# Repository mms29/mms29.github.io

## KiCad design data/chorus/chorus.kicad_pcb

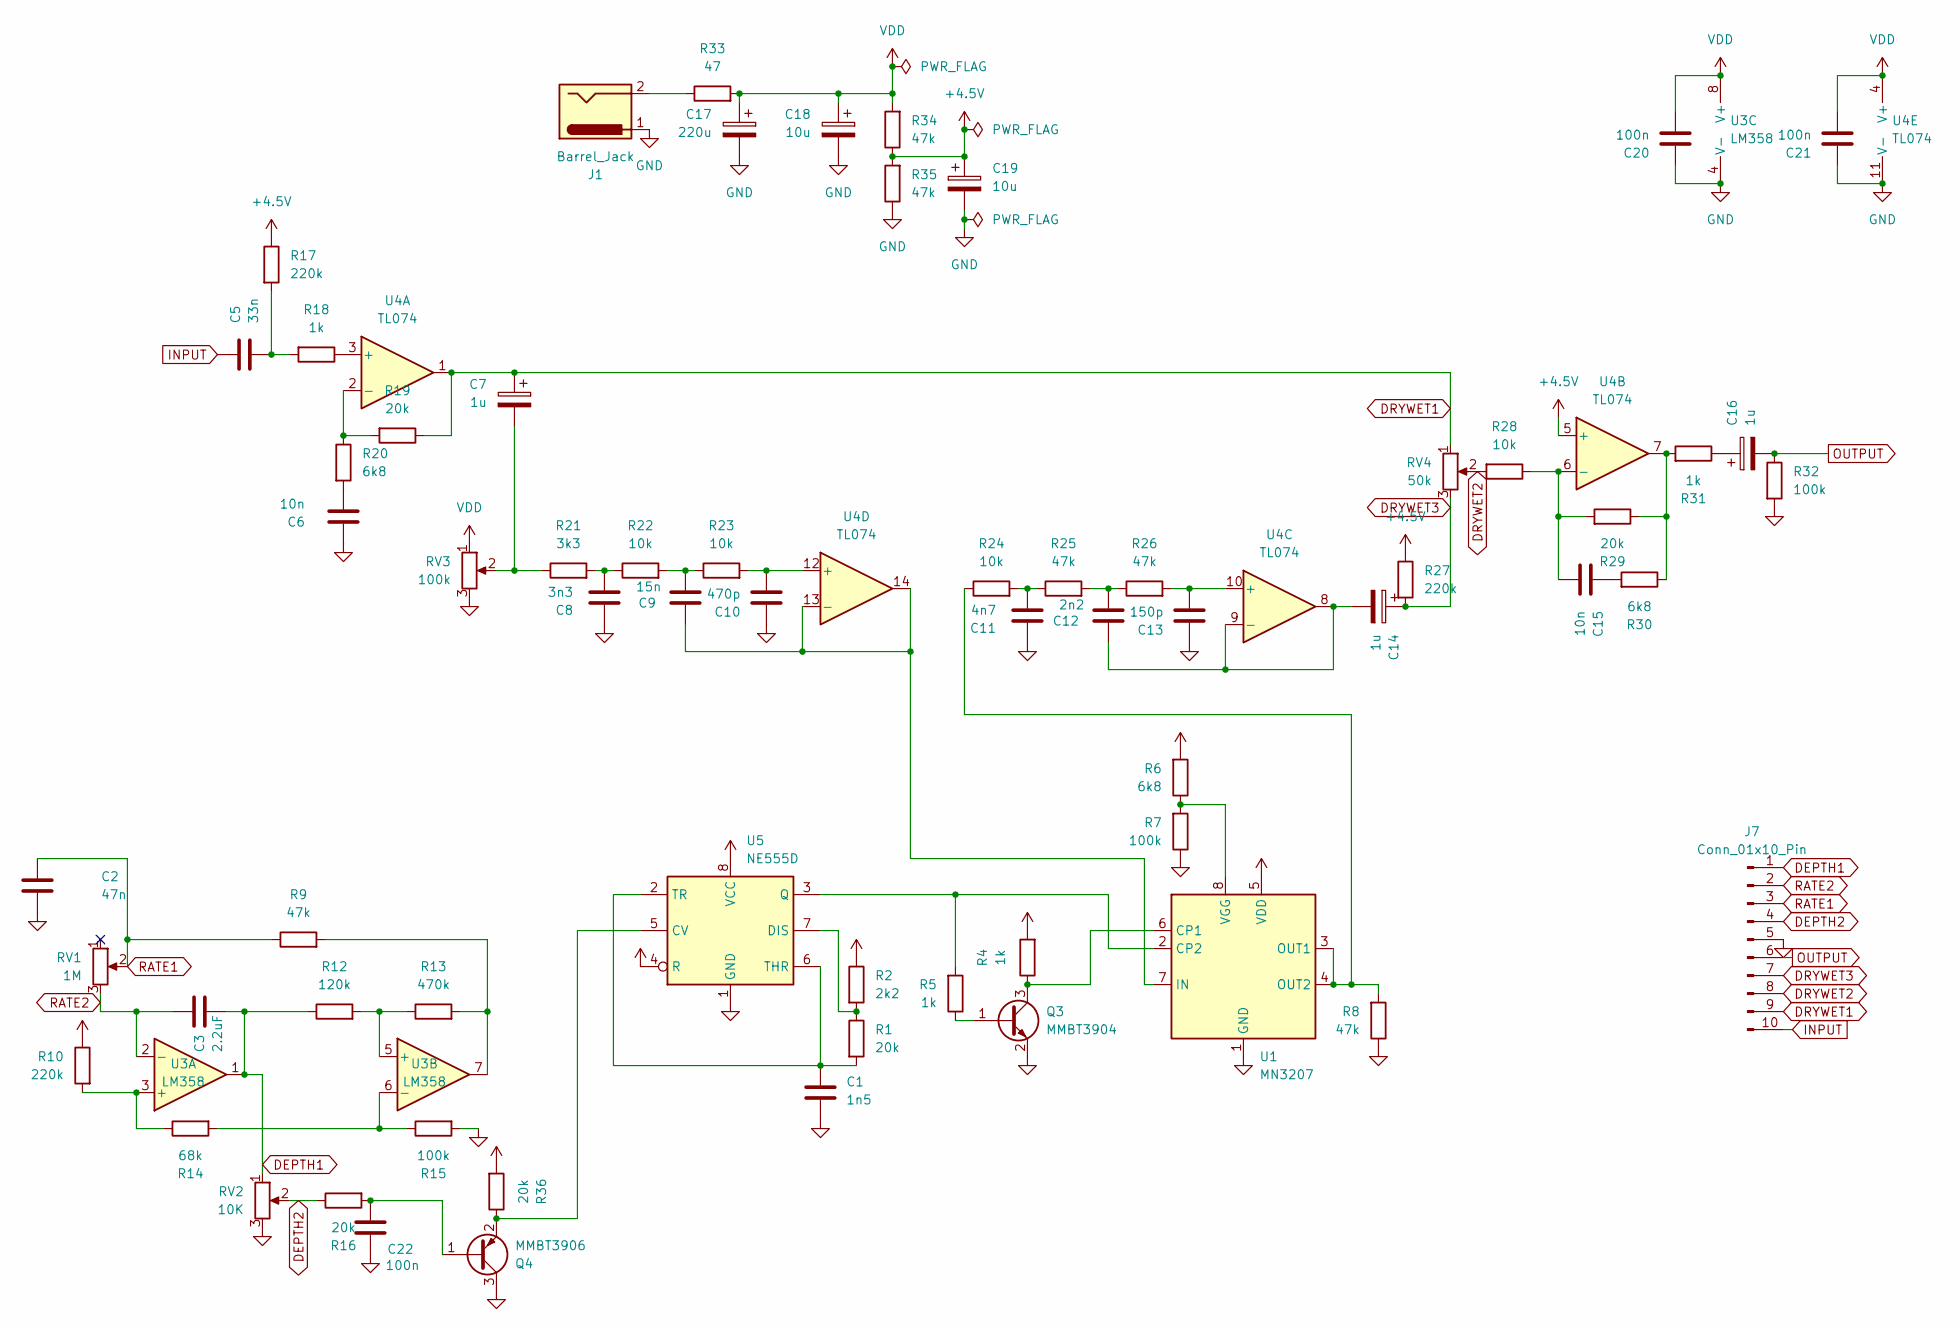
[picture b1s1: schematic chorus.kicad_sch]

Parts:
C1: 1n5; R_0603_1608Metric
C2: 47n; R_0603_1608Metric
C3: 2.2uF; R_0603_1608Metric
C5: 33n; R_0603_1608Metric
C6: 10n; R_0603_1608Metric
C7, C14, C16: 1u; CP_EIA-3216-10_Kemet-I
C8: 3n3; C_0603_1608Metric
C9: 15n; C_0603_1608Metric
C10: 470p; C_0603_1608Metric
C11: 4n7; C_0603_1608Metric
C12: 2n2; C_0603_1608Metric
C13: 150p; C_0603_1608Metric
C15: 10n; C_0603_1608Metric
C17: 220u; CP_Elec_6.3x7.7
C18, C19: 10u; C_1206_3216Metric
C20, C21, C22: 100n; C_0603_1608Metric
J1: Barrel_Jack; PinSocket_2x01_P2.54mm_Vertical
J7: Conn_01x10_Pin; PinHeader_1x10_P2.54mm_Vertical
Q3: MMBT3904; SOT-23
Q4: MMBT3906; SOT-23
R1, R16, R19, R29, R36: 20k; R_0603_1608Metric
R2: 2k2; R_0603_1608Metric
R4, R5, R18, R31: 1k; R_0603_1608Metric
R6, R20, R30: 6k8; R_0603_1608Metric
R7, R15, R32: 100k; R_0603_1608Metric
R8, R9, R25, R26, R34, R35: 47k; R_0603_1608Metric
R10, R17, R27: 220k; R_0603_1608Metric
R12: 120k; R_0603_1608Metric
R13: 470k; R_0603_1608Metric
R14: 68k; R_0603_1608Metric
R21: 3k3; R_0603_1608Metric
R22, R23, R24, R28: 10k; R_0603_1608Metric
R33: 47; R_0603_1608Metric
RV1: 1M; Potentiometer_Omeg_PC16BU_Vertical
RV2: 10K; Potentiometer_Omeg_PC16BU_Vertical
RV3: 100k; Potentiometer_Bourns_3314J_Vertical
RV4: 50k; Potentiometer_Omeg_PC16BU_Vertical
U1: MN3207; DIP-8-16_W7.62mm
U3: LM358; SOIC-8_3.9x4.9mm_P1.27mm
U4: TL074; SOIC-14_3.9x8.7mm_P1.27mm
U5: NE555D; SOIC-8_3.9x4.9mm_P1.27mm

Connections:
+4.5V: C19.1, R17.1, R27.1, R34.1, R35.2, U4.5 (+)
DEPTH1: C3.2, J7.1, R12.1, RV2.1, U3.1
DEPTH2: J7.4, R16.1, RV2.2
DRYWET1: C7.1, J7.9, R19.1, RV4.1, U4.1
DRYWET2: J7.8, R28.2, RV4.2
DRYWET3: C14.1, J7.7, R27.2, RV4.3
GND: C1.2, C2.2, C6.1, C8.1, C10.1, C11.1, C13.1, C17.2, C18.2, C19.2, C20.1, C21.1, C22.2, J1.1, J7.5, Q3.2 (E), Q4.3 (C), R7.1, R8.1, R15.2, R32.2, R35.1, RV2.3, RV3.3, U1.1 (GND), U3.4 (V-), U4.11 (V-), U5.1 (GND)
INPUT: C5.1, J7.10
unnamed: C5.2, R17.2, R18.2
unnamed: C6.2, R20.2
unnamed: C7.2, R21.1, RV3.2
unnamed: C8.2, R21.2, R22.1
unnamed: C9.2, R22.2, R23.1
unnamed: C11.2, R24.2, R25.1
unnamed: C12.2, R25.2, R26.1
unnamed: C15.1, R30.2
unnamed: C16.1, R31.1
unnamed: J1.2, R33.1
unnamed: Q3.1 (B), R5.1
unnamed: Q3.3 (C), R4.1, U1.6 (CP1)
unnamed: C22.1, Q4.1 (B), R16.2
unnamed: Q4.2 (E), R36.1, U5.5 (CV)
unnamed: R9.2, R13.2, U3.7
unnamed: R29.1, R30.1, R31.2, U4.7
unnamed: R5.2, U1.2 (CP2), U5.3 (Q)
unnamed: C9.1, U1.7 (IN), U4.13 (-), U4.14
unnamed: R8.2, R24.1, U1.3 (OUT1), U1.4 (OUT2)
unnamed: R6.1, R7.2, U1.8 (VGG)
unnamed: R10.2, R14.1, U3.3 (+)
unnamed: R12.2, R13.1, U3.5 (+)
unnamed: R14.2, R15.1, U3.6 (-)
unnamed: R18.1, U4.3 (+)
unnamed: R19.2, R20.1, U4.2 (-)
unnamed: C15.2, R28.1, R29.2, U4.6 (-)
unnamed: C13.2, R26.2, U4.10 (+)
unnamed: C12.1, C14.2, U4.8, U4.9 (-)
unnamed: C10.2, R23.2, U4.12 (+)
unnamed: R1.1, R2.2, U5.7 (DIS)
unnamed: C1.1, R1.2, U5.2 (TR), U5.6 (THR)
OUTPUT: C16.2, J7.6, R32.1
RATE1: C2.1, J7.3, R9.1, RV1.2
RATE2: C3.1, J7.2, RV1.3, U3.2 (-)
VDD: C17.1, C18.1, C20.2, C21.2, R2.1, R4.2, R6.2, R10.1, R33.2, R34.2, R36.2, RV3.1, U1.5 (VDD), U3.8 (V+), U4.4 (V+), U5.4 (R), U5.8 (VCC)

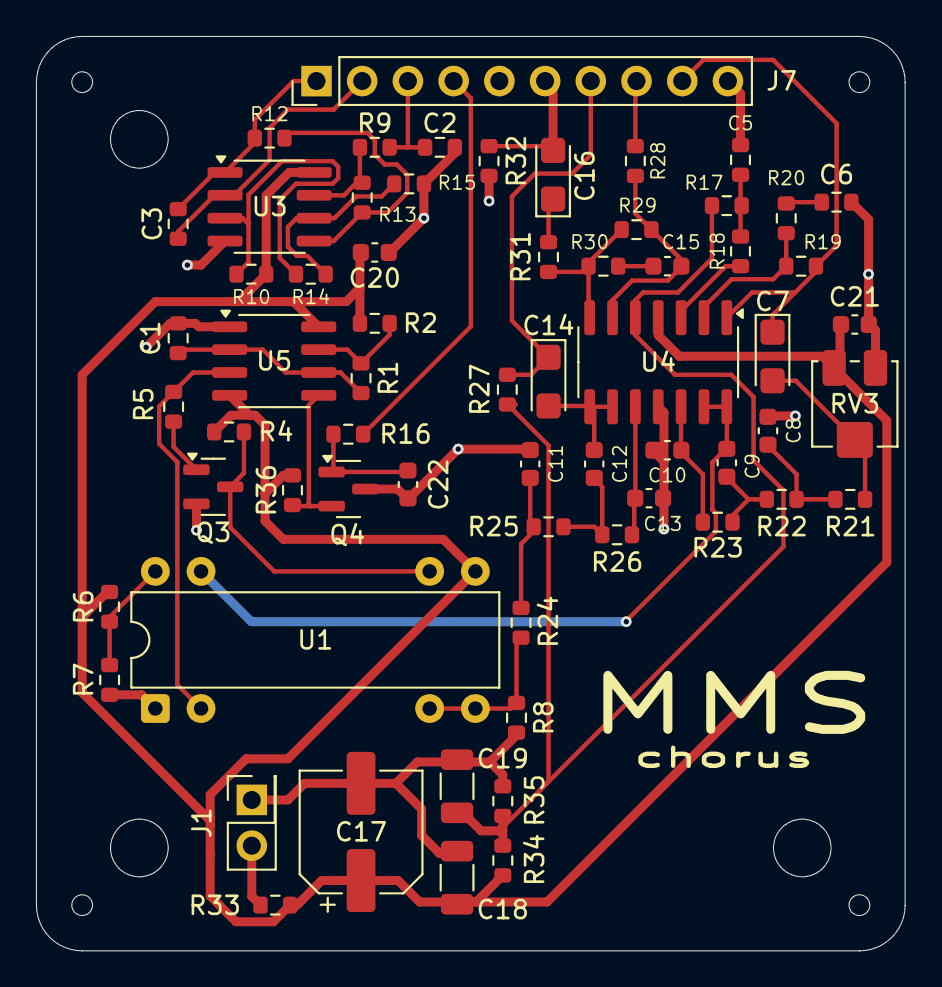
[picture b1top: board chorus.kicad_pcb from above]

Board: 2 copper layers, 48.3 x 50.8 mm, 64 parts (0 on the bottom side), 43 nets.

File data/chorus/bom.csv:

"Reference","Value","Datasheet","Footprint","Qty","DNP"
"C1","1n5","~","Resistor_SMD:R_0603_1608Metric","1",""
"C2,C3","47n","~","Resistor_SMD:R_0603_1608Metric","2",""
"C5","33n","~","Resistor_SMD:R_0603_1608Metric","1",""
"C6,C15","10n","~","Resistor_SMD:R_0603_1608Metric","2",""
"C7,C14,C16","1u","~","Capacitor_Tantalum_SMD:CP_EIA-3216-10_Kemet-I","3",""
"C8","3n3","~","Resistor_SMD:R_0603_1608Metric","1",""
"C9","15n","~","Resistor_SMD:R_0603_1608Metric","1",""
"C10","470p","~","Resistor_SMD:R_0603_1608Metric","1",""
"C11","4n7","~","Resistor_SMD:R_0603_1608Metric","1",""
"C12","2n2","~","Resistor_SMD:R_0603_1608Metric","1",""
"C13","150p","~","Resistor_SMD:R_0603_1608Metric","1",""
"C17","220u","~","Capacitor_SMD:CP_Elec_6.3x7.7","1",""
"C18,C19","10u","~","Capacitor_Tantalum_SMD:CP_EIA-3216-10_Kemet-I","2",""
"C20,C21,C22","100n","~","Resistor_SMD:R_0603_1608Metric","3",""
"Q3","MMBT3904","https://www.onsemi.com/pdf/datasheet/pzt3904-d.pdf","Package_TO_SOT_SMD:SOT-23","1",""
"Q4","MMBT3906","https://www.onsemi.com/pdf/datasheet/pzt3906-d.pdf","Package_TO_SOT_SMD:SOT-23","1",""
"R1,R16,R19,R29,R36","20k","~","Resistor_SMD:R_0603_1608Metric","5",""
"R2","2k2","~","Resistor_SMD:R_0603_1608Metric","1",""
"R4,R5,R18,R31","1k","~","Resistor_SMD:R_0603_1608Metric","4",""
"R6,R20,R30","6k8","~","Resistor_SMD:R_0603_1608Metric","3",""
"R7,R15,R32","100k","~","Resistor_SMD:R_0603_1608Metric","3",""
"R8,R9,R25,R26,R34,R35","47k","~","Resistor_SMD:R_0603_1608Metric","6",""
"R10,R17,R27","220k","~","Resistor_SMD:R_0603_1608Metric","3",""
"R12","120k","~","Resistor_SMD:R_0603_1608Metric","1",""
"R13","470k","~","Resistor_SMD:R_0603_1608Metric","1",""
"R14","68k","~","Resistor_SMD:R_0603_1608Metric","1",""
"R21","3k3","~","Resistor_SMD:R_0603_1608Metric","1",""
"R22,R23,R24,R28","10k","~","Resistor_SMD:R_0603_1608Metric","4",""
"R33","47","~","Resistor_SMD:R_0603_1608Metric","1",""
"RV3","100k","~","Potentiometer_SMD:Potentiometer_Bourns_3314J_Vertical","1",""
"U3","LM358","http://www.ti.com/lit/ds/symlink/lm2904-n.pdf","Package_SO:SOIC-8_3.9x4.9mm_P1.27mm","1",""
"U4","TL074","http://www.ti.com/lit/ds/symlink/tl071.pdf","Package_SO:SOIC-14_3.9x8.7mm_P1.27mm","1",""
"U5","NE555D","http://www.ti.com/lit/ds/symlink/ne555.pdf","Package_SO:SOIC-8_3.9x4.9mm_P1.27mm","1",""

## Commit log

2026-02-26 Initial site
2026-02-26 trigger redeploy
2026-02-26 deploy: 62f88f1214da70c5ab586c52fb4003767cd05ecb
2026-02-26 deploy: d365246bd3082776a93d9f9ec13b4f7842ee0fc3
2026-02-26 deploy: e384b6dd1985691b67e340d181d5e4f0fb3c97ab
2026-04-01 Change default language to French and update menu names
2026-04-01 Swap weight values for English and French languages
2026-04-01 projects chorus
2026-04-01 Update URLs in hugo.toml for menu items
2026-04-01 reorganize content
